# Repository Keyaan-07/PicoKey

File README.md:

# PicoKey 

I go to highschool, and teens are always around when i try to login to my mail or github or any other account, so my password can be compromised.  

To solve this, I created PicoKey, which is a hardware pass key in a very small form factor(34.5mm x 18.5mm). It uses the RP2350A chip, although I wanted to use my favourite MCU, the rp2040, it was not safe as a pass key, so I used the rp2350A this time, which is much more safer and secure than the RP2350A.  

I think it can also function as a USB-HID device because it has an external button too and 16Mb of memory size.

It has USB-A in the PCB itself soo need for external connectors, however, you either need to order a 2.0mm thick PCB(expensive) or you need to order a 1.6mm PCB(pretty cheap) and make up for the 0.4mm using tape or some other method.  

### Features:
> Small form factor: 3.45cm x 1.85 cm  
> Uses the latest MCU from Raspberyy Pi, the RP2350A  
> Could Potentially have HID Compatibility  
> USB inbuilt the PCB

Idea taken from ```@Rudy``` 's [RP2350 hardware key](https://github.com/Outdatedcandy92/PicoDucky)  

# How to Assemble this PCB?

It is basically a single pcb, so assembling this project means soldering on all the components.  

To solder, I would recommend buying a stencil along with the PCBs, or opting for PCBA from your PCB manufacturer, I am using [JLC](https://jlcpcb.com) for this, and I will be opting for PCBA, as this is a 2 sided board, it will be much easier for 1 side to be PCBA(bottom side) and other by hand(top side).  

The RP2350A is housed on the bottom side along with most of the components, and I have placed easy to solder components on the top, and the small pads for resistors and LED are a little bigger, which would help in soldering by hand.

# Why i chose to make this project
I chose to make this project mainly for 2 reasons:  

1. i wanted to have a secure hardware key and didn't wanna sign in using passwords in front of everyone.  

2. I wanted to try out making a 2 sided PCB(where components are on 2 sides), to learn how to make such projects and the learning curve for dual sided PCBs.  

# Images

# BOM

| ITEM NAME                   | ITEM PRICE | FUNCTION                 | URL                                       |
| --------------------------- | ---------- | ------------------------ | ----------------------------------------- |
| Pcb Manufacturing + stencil | 23.82      | main pcb and smt stencil | [https://jlcpcb.com](https://jlcpcb.com/) |
| PCB Components              | 21.1131    | components on the PCB    | [https://lcsc.com](https://lcsc.com/)     |
|  Total                  | 44.93      | USD                      |                                           |

# PCB Components Breakdown

### Note: There are a few resistors and capacitors, which had very high minimum order quantity(MOQ), about 50 pieces so i had to forcefully include those, which i will be utilising in my next highway projects. And tbh the prices were very less(about $0.02 per piece) so i think it is alright

### if DNO is yes, i am not ordering the respective parts and thus i have not included the cost in BOM.

| Id | Designator                                             | Designation   | MPN                   | Footprint                       | DNO - Do not order | MOQ | Price  | Quantity | Amount | Supplier link                                                                                                                                  |
| -- | ------------------------------------------------------ | ------------- | --------------------- | ------------------------------- | ------------------ | --- | ------ | -------- | ------ | ---------------------------------------------------------------------------------------------------------------------------------------------- |
| 1  | C1, C2, C3                                             | 4.7u          | GRM155R61C475KE15D    | 402                             | No                 | Yes | 0.057  | 10       | 0.57   | https://lcsc.com/product-detail/Multilayer-Ceramic-Capacitors-MLCC-SMD-SMT_Murata-Electronics-GRM155R61C475KE15D_C426094.html                  |
| 2  | C10, C11, C12, C13, C14, C15, C16, C17, C6, C7, C8, C9 | 100n          | GRM155R61H104JE14D    | 402                             | Yes                | \-  | 0      | 36       | 0      | https://lcsc.com/product-detail/Multilayer-Ceramic-Capacitors-MLCC-SMD-SMT_Murata-Electronics-GRM155R61H104JE14D_C426067.html                  |
| 3  | C18, C19                                               | 15p           | GJM1555C1H150FB01D    | 402                             | Yes                | \-  | 0      | 6        | 0      | https://lcsc.com/product-detail/Multilayer-Ceramic-Capacitors-MLCC-SMD-SMT_Murata-Electronics-GJM1555C1H150FB01D_C441742.html                  |
| 4  | C4, C5                                                 | 10u           | CL21A106KBVNNNE       | 805                             | No                 | Yes | 0.046  | 5        | 0.23   | https://lcsc.com/product-detail/Multilayer-Ceramic-Capacitors-MLCC-SMD-SMT_Samsung-Electro-Mechanics-CL21A106KBYQNNE_C2932476.html             |
| 5  | D1                                                     | LED           | 19-213-GHC-YR1S1N-3T  | 402                             | Yes                | \-  | 0      | 3        | 0      | https://www.lcsc.com/product-detail/LED-Indication-Discrete_Everlight-Elec-16-213-GHC-YR1S1N-3T_C2980183.html?s_z=n_LED                        |
| 6  | D2                                                     | ESDS314DBVR   | ESD5314DBVR           | 402                             | No                 | Yes | 0.212  | 5        | 1.06   | https://lcsc.com/product-detail/ESD-and-Surge-Protection-TVS-ESD_TI-ESDS314DBVR_C1847859.html                                                  |
| 7  | J1                                                     | USB_A         | \-                    | USBPCB                          | On PCB             | \-  | \-     | \-       | \-     | \-                                                                                                                                             |
| 8  | L1                                                     | 3.3u          | A201610S3R3-101-T     | 806                             | No                 | Yes | 0.2592 | 5        | 1.3    | https://lcsc.com/product-detail/Power-Inductors_Abracon-LLC-AOTA-B201610S3R3-101-T_C42411119.html                                              |
| 9  | R1                                                     | 33            | RT0402BRD0733RL       | 402                             | No                 | Yes | 0.0198 | 50       | 0.99   | https://lcsc.com/product-detail/Chip-Resistor-Surface-Mount_YAGEO-RT0402BRD0733RL_C852729.html                                                 |
| 10 | R2, R5, R6, R7                                         | 1k            | CRCW040210K0FKEDHP    | 402                             | No                 | Yes | 0.023  | 20       | 0.46   | https://lcsc.com/product-detail/Chip-Resistor-Surface-Mount_Vishay-Intertech-CRCW04021K00FKEDHP_C313354.html                                   |
| 11 | R3, R4                                                 | 27            | ERJ2GEJ270X           | 402                             | Yes                | \-  | 0      | 6        | 0      | https://lcsc.com/product-detail/Chip-Resistor-Surface-Mount_PANASONIC-ERJ2GEJ270X_C278580.html                                                 |
| 12 | SW1, SW2                                               | SW_Push       | K-PTS810SJMS205MTLFSG | SW_SPST_PTS810                  | No                 | No  | 0.6    | 6        | 3.6    | https://lcsc.com/product-detail/Tactile-Switches_C-K-PTS810SJM250SMTRLFS_C116501.html                                                          |
| 13 | U1                                                     | RP2350A-QFN60 | RPi2350               | QFN-60                          | No                 | No  | 1.514  | 3        | 4.542  | https://www.silverlineelectronics.in/collections/the-raspberry-pi/products/rp2350a-raspberry-pi-microcontroller-chip-in-stock-silverline-india |
| 14 | U2                                                     | AMS1117S-3.3  | AMS1117-3.3           | SOT-89-3                        | No                 | Yes | 0.1    | 5        | 0.5    | https://lcsc.com/product-detail/Voltage-Regulators-Linear-Low-Drop-Out-LDO-Regulators_JSMSEMI-AMS1117S-3-3_C917152.html                        |
| 15 | U3                                                     | W25Q128JVS    | W25Q128JVSIM          | SOIC-8_5.3x5.3mm_P1.27mm        | Yes                | \-  | 0      | 3        | 0      | https://lcsc.com/product-detail/NOR-FLASH_Winbond-Elec-W25Q128JVSIM_C2613930.html                                                              |
| 16 | Y1                                                     | Crystal_GND24 | ABM8-27-T3            | Crystal_SMD_3225-4Pin_3.2x2.5mm | No                 | No  | 0.3737 | 3        | 1.1211 | https://www.lcsc.com/product-detail/Crystals_Abracon-LLC-ABM8-272-T3_C20625731.html?s_z=n_abm8                                                 |
|    |                                                        | Shipping      | 3.74                  |                                 |                    |     |        |          |        |                                                                                                                                                |
|    |                                                        | Handling fee  | 3                     |                                 |                    |     |        |          |        |                                                                                                                                                |
|    |                                                        | Total         | 21.1131               | USD                             |                    |     |        |          |        |                                                                                                                                                |

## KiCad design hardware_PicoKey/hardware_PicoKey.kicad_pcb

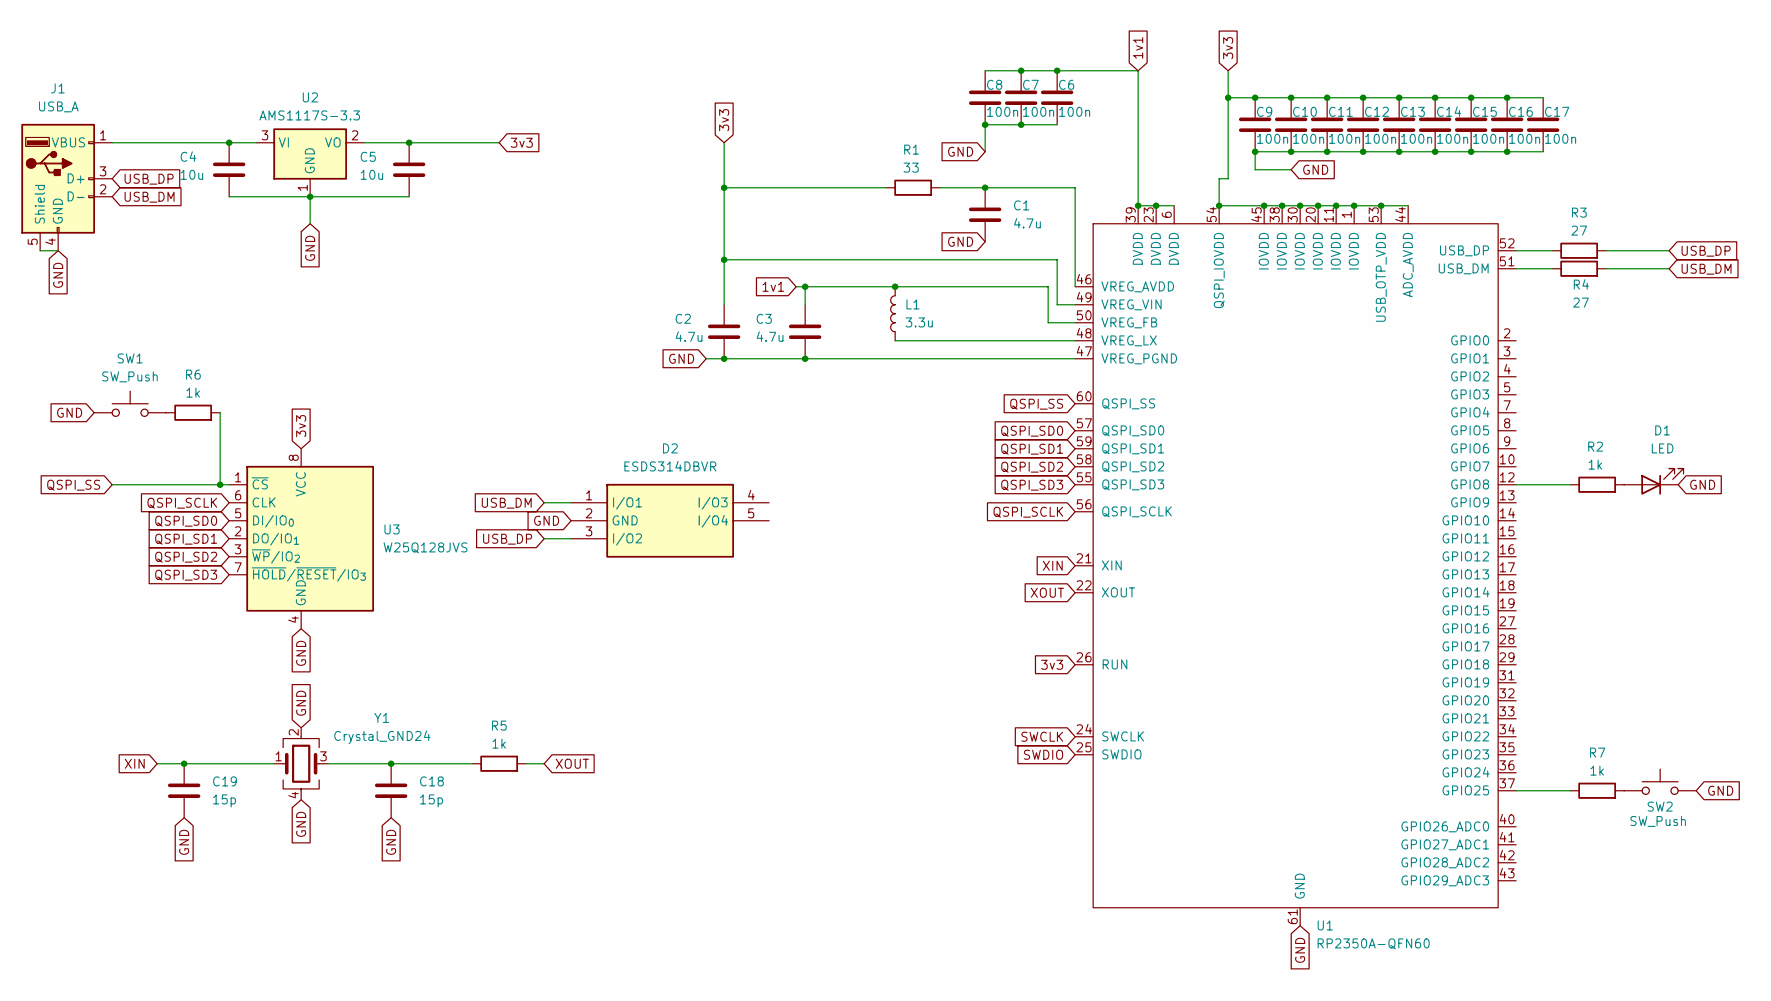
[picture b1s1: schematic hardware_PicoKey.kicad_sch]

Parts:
C1, C2, C3: 4.7u; C_0402_1005Metric
C4, C5: 10u; C_0805_2012Metric
C6, C7, C8, C9, C10, C11, C12, C13, C14, C15, C16, C17: 100n; C_0402_1005Metric
C18, C19: 15p; C_0402_1005Metric
D1: LED; LED_0402_1005Metric_Pad0.77x0.64mm_HandSolder
D2: ESDS314DBVR; ESDS314BVR_SOT95P280X145-5N; Mouser Part Number 595-ESDS314DBVR
J1: USB_A; USBPCB
L1: 3.3u; L_0805_2012Metric
R1: 33; R_0402_1005Metric
R2, R6, R7: 1k; R_0402_1005Metric_Pad0.72x0.64mm_HandSolder
R3, R4: 27; R_0402_1005Metric
R5: 1k; R_0402_1005Metric
SW1, SW2: SW_Push; SW_SPST_PTS810
U1: RP2350A-QFN60; RP2350A_QFN-60_EP_7.75x7.75_Pitch0.4mm
U2: AMS1117S-3.3; SOT-89-3
U3: W25Q128JVS; SOIC-8_5.3x5.3mm_P1.27mm
Y1: Crystal_GND24; Crystal_SMD_3225-4Pin_3.2x2.5mm

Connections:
1v1: C3.1, C6.1, C7.1, C8.1, L1.2, U1.6 (DVDD), U1.23 (DVDD), U1.39 (DVDD), U1.50 (VREG_FB)
3v3: C2.1, C5.1, C9.1, C10.1, C11.1, C12.1, C13.1, C14.1, C15.1, C16.1, C17.1, R1.1, U1.1 (IOVDD), U1.11 (IOVDD), U1.20 (IOVDD), U1.26 (RUN), U1.30 (IOVDD), U1.38 (IOVDD), U1.44 (ADC_AVDD), U1.45 (IOVDD), U1.49 (VREG_VIN), U1.53 (USB_OTP_VDD), U1.54 (QSPI_IOVDD), U2.2 (VO), U3.8 (VCC)
GND: C1.2, C2.2, C3.2, C4.2, C5.2, C6.2, C7.2, C8.2, C9.2, C10.2, C11.2, C12.2, C13.2, C14.2, C15.2, C16.2, C17.2, C18.2, C19.2, D1.1 (K), D2.2 (GND), J1.4 (GND), J1.5 (Shield), SW1.1, SW2.2, U1.47 (VREG_PGND), U1.61 (GND), U2.1 (GND), U3.4 (GND), Y1.2, Y1.4
unnamed: C18.1, R5.1, Y1.3
unnamed: D1.2 (A), R2.2
unnamed: C4.1, J1.1 (VBUS), U2.3 (VI)
unnamed: R6.1, SW1.2
unnamed: R7.2, SW2.1
unnamed: R2.1, U1.12 (GPIO8)
unnamed: R7.1, U1.37 (GPIO25)
unnamed: R4.1, U1.51 (USB_DM)
unnamed: R3.1, U1.52 (USB_DP)
unnamed: C1.1, R1.2, U1.46 (VREG_AVDD)
unnamed: L1.1, U1.48 (VREG_LX)
QSPI_SCLK: U1.56 (QSPI_SCLK), U3.6 (CLK)
QSPI_SD0: U1.57 (QSPI_SD0), U3.5 (DI/IO_{0})
QSPI_SD1: U1.59 (QSPI_SD1), U3.2 (DO/IO_{1})
QSPI_SD2: U1.58 (QSPI_SD2), U3.3 (~WP/IO_{2})
QSPI_SD3: U1.55 (QSPI_SD3), U3.7 (~HOLD/~RESET/IO_{3})
QSPI_SS: R6.2, U1.60 (QSPI_SS), U3.1 (~CS)
SWCLK: U1.24 (SWCLK)
SWDIO: U1.25 (SWDIO)
USB_DM: D2.1 (I/O1), J1.2 (D-), R4.2
USB_DP: D2.3 (I/O2), J1.3 (D+), R3.2
XIN: C19.1, U1.21 (XIN), Y1.1
XOUT: R5.2, U1.22 (XOUT)

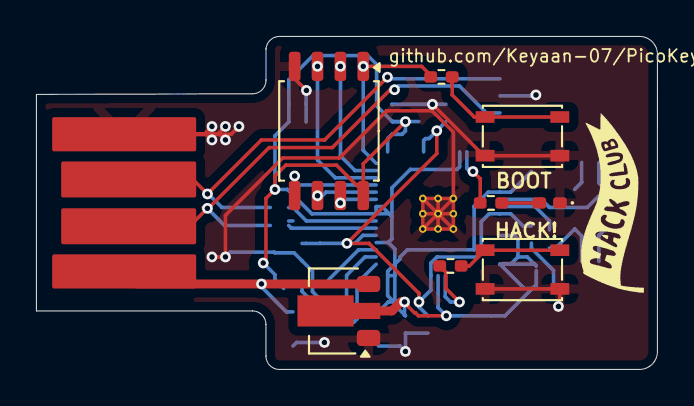
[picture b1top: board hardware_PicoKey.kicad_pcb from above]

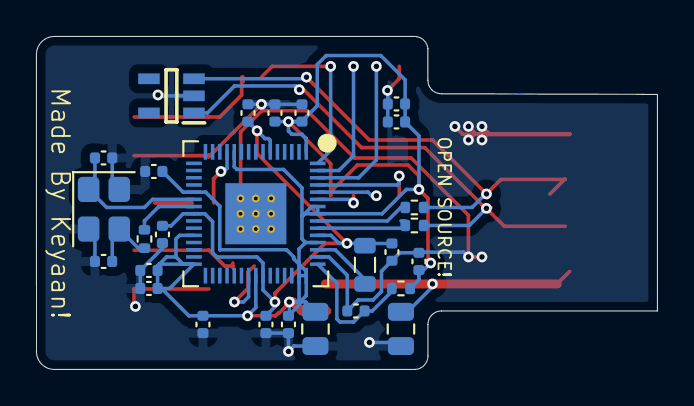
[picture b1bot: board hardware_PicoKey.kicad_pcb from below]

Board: 2 copper layers, 34.5 x 18.5 mm, 36 parts (27 on the bottom side), 24 nets.

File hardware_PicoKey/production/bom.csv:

Designator,Footprint,Quantity,Value,LCSC Part #
"C1, C2, C3",0402,3,4.7u,
"C10, C11, C12, C13, C14, C15, C16, C17, C6, C7, C8, C9",0402,12,100n,
"C18, C19",0402,2,15p,
"C4, C5",0805,2,10u,
D1,0402,1,LED,
D2,ESDS314BVR_SOT95P280X145-5N,1,ESDS314DBVR,
J1,USBPCB,1,USB_A,
L1,0805,1,3.3u,
R1,0402,1,33,
"R2, R5, R6, R7",0402,4,1k,
"R3, R4",0402,2,27,
"SW1, SW2",SW_SPST_PTS810,2,SW_Push,
U1,RP2350A_QFN-60_EP_7.75x7.75_Pitch0.4mm,1,RP2350A-QFN60,
U2,SOT-89-3,1,AMS1117S-3.3,
U3,SOIC-8_5.3x5.3mm_P1.27mm,1,W25Q128JVS,
Y1,Crystal_SMD_3225-4Pin_3.2x2.5mm,1,Crystal_GND24,

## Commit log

2025-06-26 NEW PROJECTTTTTT!!!!
2025-06-27 starting the proj!!
2025-06-28 added table
2025-06-29 started with schematic
2025-06-29 add footprints for rp2350A and rp2350B
2025-06-29 journaling
2025-06-30 schematic
2025-06-30 image
2025-06-30 time spent - journaling
2025-07-01 journal
2025-07-01 new thing to do
2025-07-01 schematic doneee
2025-07-01 iamges
2025-07-01 sch + pcb
2025-07-01 ESD protection IC
2025-07-01 update time spent
2025-07-01 idk backups probably
2025-07-01 beautifying~~~
2025-07-01 images and journaling
2025-07-02 'pcb'
2025-07-02 images
2025-07-04 'Update'
2025-07-04 pcb and journaling
2025-07-05 pcb donee
2025-07-05 images upload
2025-07-07 README
2025-07-07 update to inductor
2025-07-07 images updated
2025-07-09 README update
2025-07-10 pcb and BOM
2025-07-11 pcb compoents added
2025-07-11 BOM Update
2025-07-11 final commit prolly
2025-07-11 Create LICENSE
